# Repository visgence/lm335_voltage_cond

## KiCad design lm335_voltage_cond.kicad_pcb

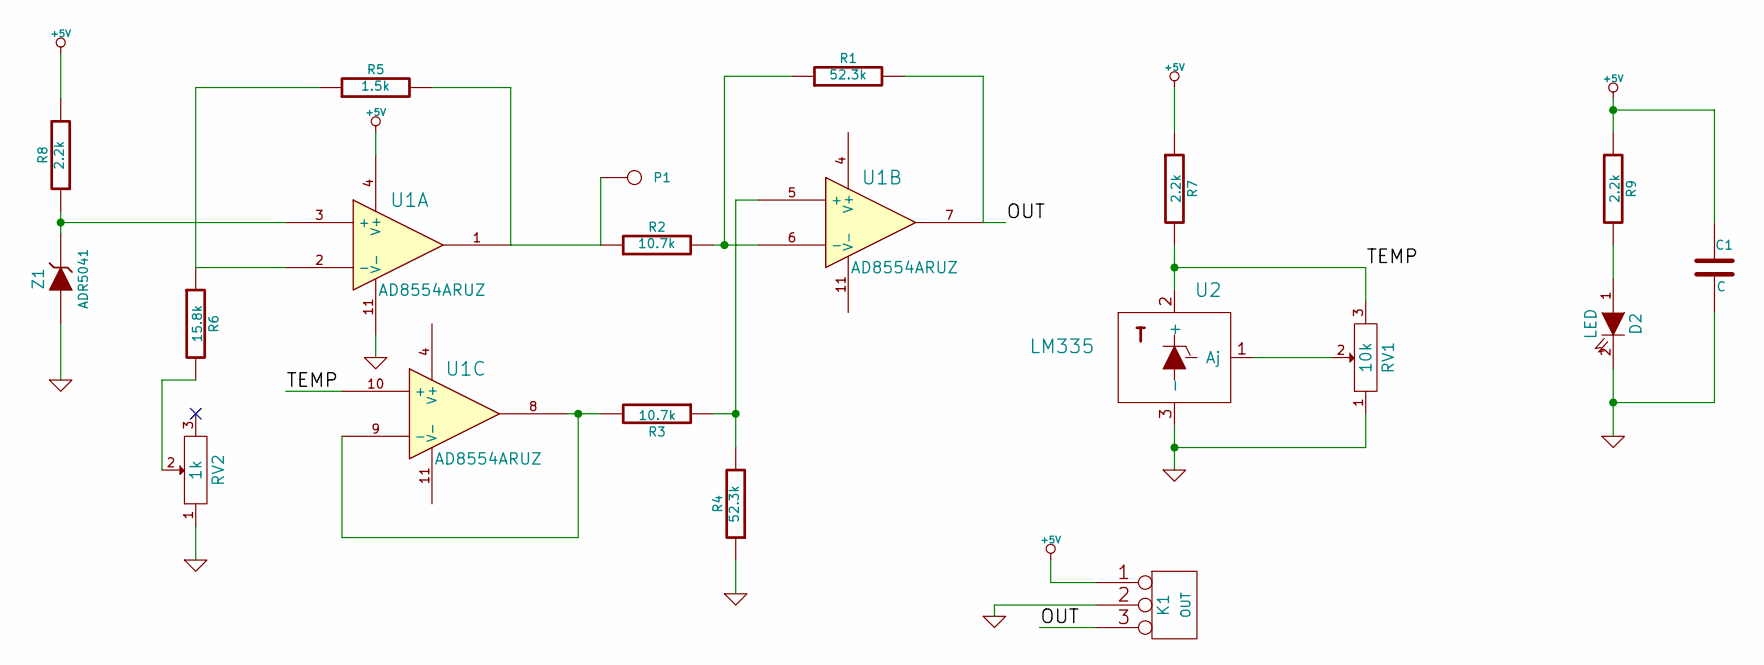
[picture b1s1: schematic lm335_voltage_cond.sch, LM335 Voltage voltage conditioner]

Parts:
C1: C
D2: LED
K1: OUT
P1: CONN_1
R1, R4: 52.3k
R2, R3: 10.7k
R5: 1.5k
R6: 15.8k
R7, R8, R9: 2.2k
RV1: 10k
RV2: 1k
U1: AD8554ARUZ
U2: LM335
Z1: ADR5041

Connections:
+5V: C1.1, K1.1, R7.1, R8.2, R9.1, U1.4 (V+)
/OUT: K1.3, R1.2, U1.7
/TEMP: R7.2, RV1.3, U1.10 (+), U2.2 (+)
GND: C1.2, D2.2 (K), K1.2 (PM), R4.1, RV1.1, RV2.1, U1.11 (V-), U2.3 (-), Z1.2 (A)
unnamed: R6.2, RV2.2
unnamed: RV1.2, U2.1 (Aj)
unnamed: R8.1, U1.3 (+), Z1.1 (K)
unnamed: D2.1 (A), R9.2
unnamed: P1.1, R2.1, R5.2, U1.1
unnamed: R5.1, R6.1, U1.2 (-)
unnamed: R1.1, R2.2, U1.6 (-)
unnamed: R3.2, U1.8, U1.9 (-)
unnamed: R3.1, R4.2, U1.5 (+)

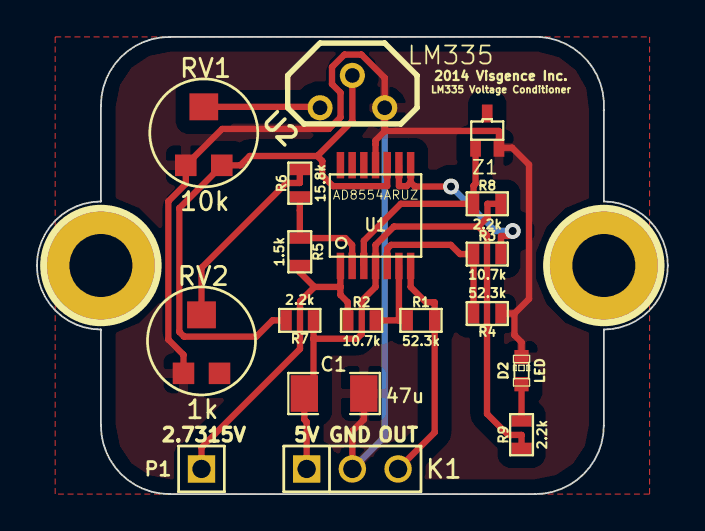
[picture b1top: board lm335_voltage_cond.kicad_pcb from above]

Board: 2 copper layers, 35.1 x 25.4 mm, 20 parts (0 on the bottom side), 13 nets.

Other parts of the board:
h1, h2: pin; 1pin_C

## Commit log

2014-01-11 Create Schematic
2014-01-11 Added netlist
2014-01-11 Did some routing
2014-01-12 Added PCB
2014-01-12 Routed board
